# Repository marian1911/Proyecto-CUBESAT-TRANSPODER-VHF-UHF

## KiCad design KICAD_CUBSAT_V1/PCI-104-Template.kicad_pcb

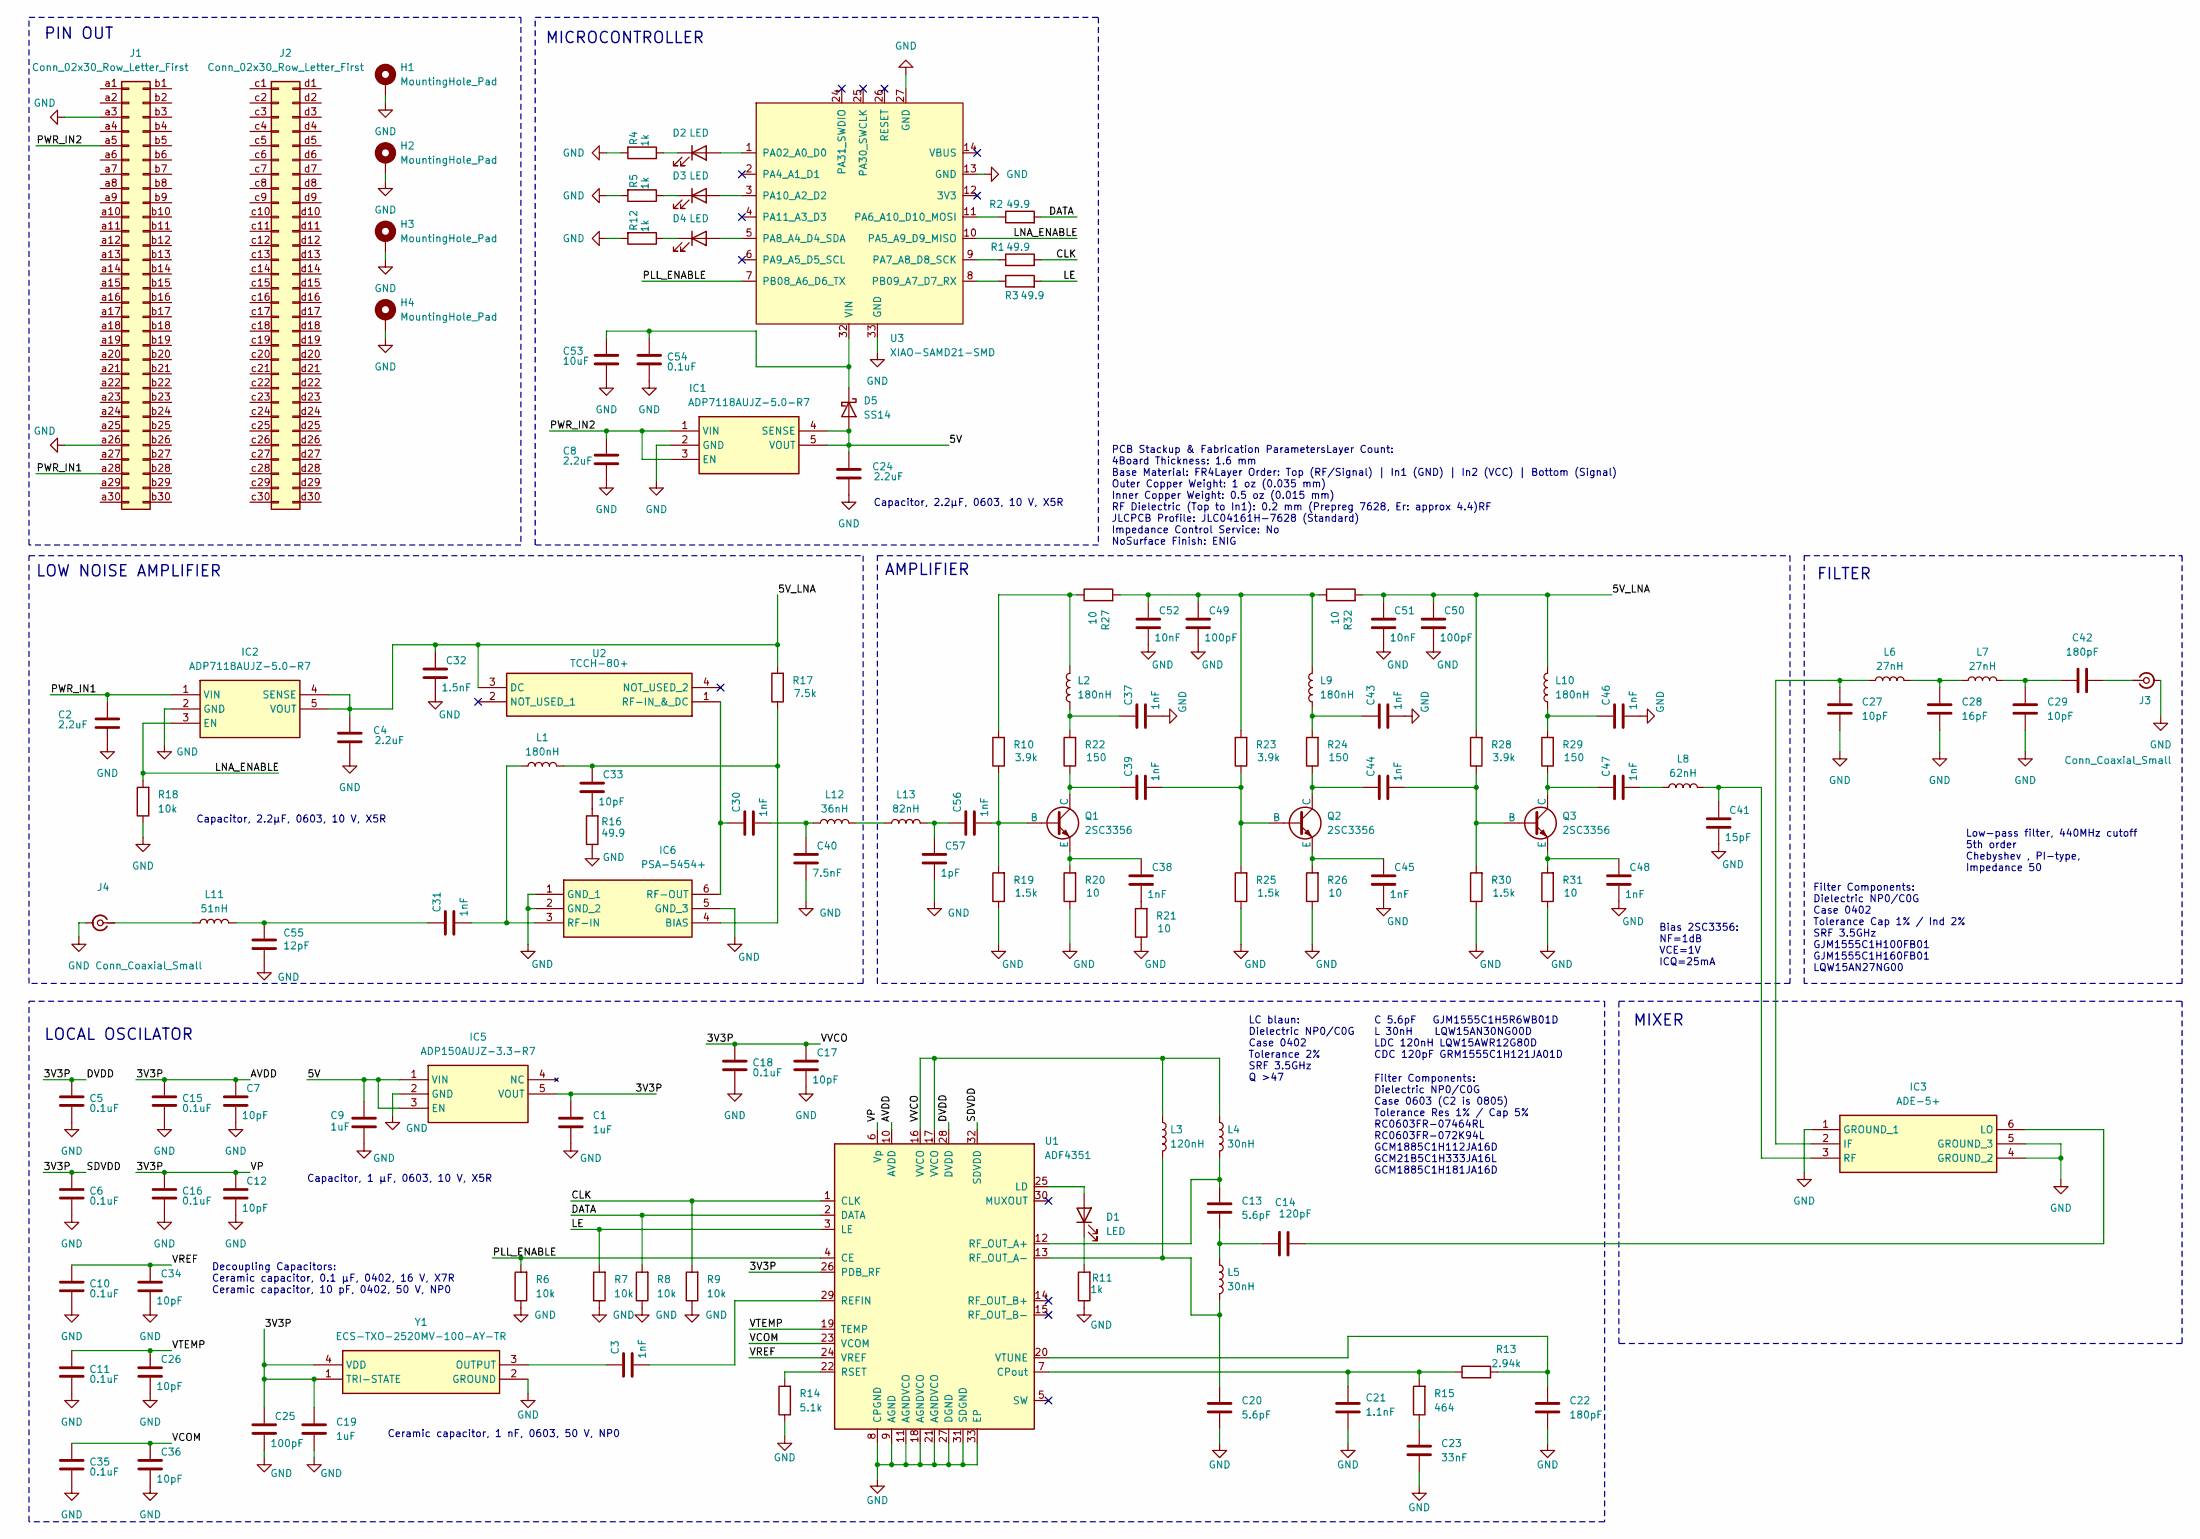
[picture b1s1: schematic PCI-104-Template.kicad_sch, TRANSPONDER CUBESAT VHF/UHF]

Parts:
C1, C9, C19: 1uF; C_0603_1608Metric; Mouser Part Number 81-GRM185R61A105KE26
C2, C4, C8, C24: 2.2uF; C_0603_1608Metric; Mouser Part Number 81-GRM188R61C225KADJ
C3, C30, C31, C37, C38, C39, C43, C44, C45, C46, C47, C48, C56: 1nF; C_0603_1608Metric; Manufacturer_Part_Number GRM1885C1H102JA01D; Mouser Part Number 81-GRM39C102J50
C5, C6, C10, C11, C15, C16, C18, C35, C54: 0.1uF; C_0402_1005Metric; Manufacturer_Part_Number GRM155R71C104KA88D; Mouser Part Number 81-GRM155R71C104KA88
C7, C12, C17, C26, C33, C34, C36: 10pF; C_0402_1005Metric; Manufacturer_Part_Number GRM1555C1H100JA01D; Mouser Part Number 81-GRM1555C1H100JA1D
C13, C20: 5.6pF; C_0402_1005Metric; Manufacturer_Part_Number GJM1555C1H5R6WB01D; Mouser Part Number 81-GJM1555C1H5R6WB1D
C14: 120pF; C_0402_1005Metric; Mouser Part Number 81-GRM1555C1H121JA01
C21: 1.1nF; C_0603_1608Metric; Mouser Part Number 81-GCM1885C1H112JA6D
C22, C42: 180pF; C_0603_1608Metric; Mouser Part Number 81-GCM1885C1H181J16D
C23: 33nF; C_0805_2012Metric; Mouser Part Number 81-GCM21B5C2A333GE2L
C25, C49, C50: 100pF; C_0402_1005Metric; Manufacturer_Part_Number GRM1885C1H101JA01D; Mouser Part Number 81-GRM39C101J50
C27, C29: 10pF; C_0402_1005Metric; Manufacturer_Part_Number GJM1555C1H100FB01D; Mouser Part Number 81-GJM1555C1H100FB01
C28: 16pF; C_0402_1005Metric; Manufacturer_Part_Number GJM1555C1H160FB01J; Mouser Part Number 81-GJM1555C1H160FB1J
C32: 1.5nF; C_0603_1608Metric; Manufacturer_Part_Number GRM1885C1H152JA01J; Mouser Part Number 81-GRM185C1H152JA01J
C40: 7.5nF; C_0603_1608Metric; Manufacturer_Part_Number GRM0225C1E7R5BA03L; Mouser Part Number 81-GRM0225C1E7R5BA3L
C41: 15pF; C_0402_1005Metric; Manufacturer_Part_Number GJM0225C1E150GB01L; Mouser Part Number 81-GJM0225C1E150GB1L
C51, C52: 10nF; C_0402_1005Metric; Manufacturer_Part_Number GRM1885C1H103JA01D; Mouser Part Number 81-GRM1885C1H103JA1D
C53: 10uF; C_0805_2012Metric; Mouser Part Number 81-GRT21BR61E106KE3L
C55: 12pF; C_0402_1005Metric; Manufacturer_Part_Number GJM0225C1C120JB01L; Mouser Part Number 81-GJM0225C1C120JB1L
C57: 1pF; C_0603_1608Metric; Manufacturer_Part_Number GJM0225C1E1R0CB01L; Mouser Part Number 81-GJM0225C1E1R0CB1L
D1, D2, D3, D4: LED; LED_0603_1608Metric; Manufacturer_Part_Number LTST-C190GKT; Mouser Part Number 859-LTST-C190GKT
D5: SS14; D_SMA; Mouser Part Number 512-SS14
H1, H2, H3, H4: MountingHole_Pad; MountingHole_3.2mm_M3_Pad_TopBottom
IC1, IC2: ADP7118AUJZ-5.0-R7; SOT95P280X100-5N; Mouser Part Number 584-ADP7118AUJZ5.0R7
IC3: ADE-5+; ADE5; Mouser Part Number 139-ADE-5
IC5: ADP150AUJZ-3.3-R7; SOT95P280X100-5N; Mouser Part Number 584-ADP150AUJZ3.3R7
IC6: PSA-5454+; SOT65P215X100-6N; Mouser Part Number 139-PSA-5454
J1, J2: Conn_02x30_Row_Letter_First; PinSocket_2x30_P2.00mm_Vertical
J3, J4: Conn_Coaxial_Small; SMA_Samtec_SMA-J-P-H-ST-EM1_EdgeMount; Manufacturer_Part_Number SMA-J-P-H-ST-EM1; Mouser Part Number 200-SMAJPHSTEM1
L1, L2, L9, L10: 180nH; L_0402_1005Metric; Manufacturer_Part_Number LQW15AWR18J80D; Mouser Part Number 81-LQW15AWR18J80D
L3: 120nH; L_0402_1005Metric; Manufacturer_Part_Number LQW15AWR12G80D; Mouser Part Number 81-LQW15AWR12G80D
L4, L5: 30nH; L_0402_1005Metric; Manufacturer_Part_Number LQW15AN30NG00D; Mouser Part Number 81-LQW15AN30NG00D
L6, L7: 27nH; L_0402_1005Metric; Manufacturer_Part_Number LQW15AN27NG00D; Mouser Part Number 81-LQW15AN27NG00D
L8: 62nH; L_0402_1005Metric; Manufacturer_Part_Number LQW15AN62NJ0ZD; Mouser Part Number 81-LQW15AN62NJ0ZD
L11: 51nH; L_0402_1005Metric; Manufacturer_Part_Number LQW15AN51NH0ZD; Mouser Part Number 81-LQW15AN51NH0ZD
L12: 36nH; L_0402_1005Metric; Manufacturer_Part_Number LQW15AN36NG80D; Mouser Part Number 81-LQW15AN36NG80D
L13: 82nH; L_0402_1005Metric; Manufacturer_Part_Number LQW15AW82NG80D; Mouser Part Number 81-LQW15AW82NG80D
Q1, Q2, Q3: 2SC3356; SOT-23
R1, R2, R3, R16: 49.9; R_0603_1608Metric; Manufacturer_Part_Number TNPW060349R9FEEA; Mouser Part Number 71-TNPW060349R9FEEA
R4, R5, R11, R12: 1k; R_0603_1608Metric; Mouser Part Number 71-TNPW06031K00FHEA
R6, R7, R8, R9, R18: 10k; R_0603_1608Metric; Mouser Part Number 71-TNPW060310K0FEEA
R10, R23, R28: 3.9k; R_0603_1608Metric; Manufacturer_Part_Number MCT06030C3901FP500; Mouser Part Number 594-MCT06030C3901FP5
R13: 2.94k; R_0603_1608Metric; Manufacturer_Part_Number RC0603FR-072K94L; Mouser Part Number 603-RC0603FR-072K94L
R14: 5.1k; R_0603_1608Metric; Manufacturer_Part_Number TNPW06035K10FHTA; Mouser Part Number 71-TNPW06035K10FHTA
R15: 464; R_0603_1608Metric; Manufacturer_Part_Number RC0603FR-07464RL; Mouser Part Number 603-RC0603FR-07464RL
R17: 7.5k; R_0603_1608Metric; Manufacturer_Part_Number MCT0603MD7501BP500; Mouser Part Number 594-MCT0603MD7501BP5
R19, R25, R30: 1.5k; R_0603_1608Metric; Manufacturer_Part_Number MCT0603MC1501FP500; Mouser Part Number 594-MCT0603MC1501FP5
R20, R21, R26, R27, R31, R32: 10; R_0603_1608Metric; Manufacturer_Part_Number MCT06030C1009FP500; Mouser Part Number 594-MCT06030C1009FP5
R22, R24, R29: 150; R_0603_1608Metric; Manufacturer_Part_Number MCT06030C1500FP500; Mouser Part Number 594-MCT06030C1500FP5
U1: ADF4351; LFCSP-32-1EP_5x5mm_P0.5mm_EP3.25x3.25mm; Manufacturer_Part_Number ADF4351BCPZ; Mouser Part Number 584-ADF4351BCPZ
U2: TCCH-80+; TCCH80; Mouser Part Number 139-TCCH-80
U3: XIAO-SAMD21-SMD; Manufacturer_Part_Number 102010328; Mouser Part Number 713-102010328
Y1: ECS-TXO-2520MV-100-AY-TR; ECSTXO2520MV120AYTR; Mouser Part Number 520-TXO2520MV100AYTR

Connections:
/3V3P: C1.2, C5.2, C6.2, C7.2, C12.2, C15.2, C16.2, C17.2, C18.2, C19.2, C25.2, IC5.5 (VOUT), L3.1, L4.1, U1.6 (Vp), U1.10 (AVDD), U1.16 (VVCO), U1.17 (VVCO), U1.26 (PDB_RF), U1.28 (DVDD), U1.32 (SDVDD), Y1.1 (TRI-STATE), Y1.4 (VDD)
/5V: C9.2, C24.2, D5.2 (A), IC1.4 (SENSE), IC1.5 (VOUT), IC5.1 (VIN), IC5.3 (EN)
/5V_LNA: C4.2, C32.2, C50.2, C51.2, IC2.4 (SENSE), IC2.5 (VOUT), L10.2, R17.2, R28.2, R32.2, U2.3 (DC)
/CLK: R1.2, R9.2, U1.1 (CLK)
/DATA: R2.2, R8.2, U1.2 (DATA)
/LE: R3.2, R7.2, U1.3 (LE)
/LNA_ENABLE: IC2.3 (EN), R18.2, U3.10 (PA5_A9_D9_MISO)
/PLL_ENABLE: R6.2, U1.4 (CE), U3.7 (PB08_A6_D6_TX)
/PWR_IN1: C2.2, IC2.1 (VIN), J1.a28
/PWR_IN2: C8.2, IC1.1 (VIN), IC1.3 (EN), J1.a5
/VCOM: C35.2, C36.2, U1.23 (VCOM)
/VREF: C10.2, C34.2, U1.24 (VREF)
/VTEMP: C11.2, C26.2, U1.19 (TEMP)
GND: C1.1, C2.1, C4.1, C5.1, C6.1, C7.1, C8.1, C9.1, C10.1, C11.1, C12.1, C15.1, C16.1, C17.1, C18.1, C19.1, C20.1, C21.1, C22.1, C23.1, C24.1, C25.1, C26.1, C27.1, C28.1, C29.1, C32.1, C34.1, C35.1, C36.1, C37.1, C40.1, C41.1, C43.1, C45.1, C46.1, C48.1, C49.1, C50.1, C51.1, C52.1, C53.1, C54.1, C55.1, C57.1, H1.1, H2.1, H3.1, H4.1, IC1.2 (GND), IC2.2 (GND), IC3.1 (GROUND_1), IC3.4 (GROUND_2), IC3.5 (GROUND_3), IC5.2 (GND), IC6.1 (GND_1), IC6.2 (GND_2), IC6.5 (GND_3), J1.a3, J1.a26, J3.2 (Ext), J4.2 (Ext), R4.2, R5.2, R6.1, R7.1, R8.1, R9.1, R11.1, R12.2, R14.1, R16.1, R18.1, R19.1, R20.1, R21.1, R25.1, R26.1, R30.1, R31.1, U1.8 (CPGND), U1.9 (AGND), U1.11 (AGNDVCO), U1.18 (AGNDVCO), U1.21 (AGNDVCO), U1.27 (DGND), U1.31 (SDGND), U1.33 (EP), U3.13 (GND), U3.27 (GND), U3.33 (GND), Y1.2 (GROUND)
unnamed: C13.1, C14.1, L5.1
unnamed: C23.2, R15.1
unnamed: C28.2, L6.2, L7.1
unnamed: C29.2, C42.2, L7.2
unnamed: C30.1, C40.2, L12.1
unnamed: C31.2, C55.2, L11.2
unnamed: C33.1, R16.2
unnamed: C37.2, L2.1, R22.2
unnamed: C38.1, R21.2
unnamed: C43.2, L9.1, R24.2
unnamed: C46.2, L10.1, R29.2
unnamed: C47.1, L8.1
unnamed: C49.2, C52.2, L9.2, R23.2, R27.2, R32.1
unnamed: C56.2, C57.2, L13.2
unnamed: D1.2 (A), U1.25 (LD)
unnamed: D1.1 (K), R11.2
unnamed: D2.2 (A), U3.1 (PA02_A0_D0)
unnamed: D2.1 (K), R4.1
unnamed: D3.2 (A), U3.3 (PA10_A2_D2)
unnamed: D3.1 (K), R5.1
unnamed: D4.2 (A), U3.5 (PA8_A4_D4_SDA)
unnamed: D4.1 (K), R12.1
unnamed: C53.2, C54.2, D5.1 (K), U3.32 (VIN)
unnamed: C27.2, IC3.2 (IF), L6.1
unnamed: C14.2, IC3.6 (LO)
unnamed: C41.2, IC3.3 (RF), L8.2
unnamed: C33.2, IC6.4 (BIAS), L1.2, R17.1
unnamed: C31.1, IC6.3 (RF-IN), L1.1
unnamed: C30.2, IC6.6 (RF-OUT), U2.1 (RF-IN_&_DC)
unnamed: C42.1, J3.1 (In)
unnamed: J4.1 (In), L11.1
unnamed: L2.2, R10.2, R27.1
unnamed: L12.2, L13.1
unnamed: C56.1, Q1.2 (B), R10.1, R19.2
unnamed: C39.2, Q1.1 (C), R22.1
unnamed: C38.2, Q1.3 (E), R20.2
unnamed: C39.1, Q2.2 (B), R23.1, R25.2
unnamed: C44.2, Q2.1 (C), R24.1
unnamed: C45.2, Q2.3 (E), R26.2
unnamed: C44.1, Q3.2 (B), R28.1, R30.2
unnamed: C47.2, Q3.1 (C), R29.1
unnamed: C48.2, Q3.3 (E), R31.2
unnamed: C21.2, R13.1, R15.2, U1.7 (CPout)
unnamed: C3.1, U1.29 (REFIN)
unnamed: C13.2, L4.2, U1.12 (RF_OUT_A+)
unnamed: C20.2, L3.2, L5.2, U1.13 (RF_OUT_A-)
unnamed: R14.2, U1.22 (RSET)
unnamed: C22.2, R13.2, U1.20 (VTUNE)
unnamed: R2.1, U3.11 (PA6_A10_D10_MOSI)
unnamed: R1.1, U3.9 (PA7_A8_D8_SCK)
unnamed: R3.1, U3.8 (PB09_A7_D7_RX)
unnamed: C3.2, Y1.3 (OUTPUT)

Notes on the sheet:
Capacitor, 1 µF, 0603, 10 V, X5R
Ceramic capacitor, 1 nF, 0603, 50 V, NP0
Filter Components: Dielectric NP0/C0G Case 0402 Tolerance Cap 1% / Ind 2% SRF 3.5GHz GJM1555C1H100FB01 GJM1555C1H160FB01 LQW15AN27NG00
MICROCONTROLLER
Decoupling Capacitors: Ceramic capacitor, 0.1 µF, 0402, 16 V, X7R Ceramic capacitor, 10 pF, 0402, 50 V, NP0
AMPLIFIER
C 5.6pF GJM1555C1H5R6WB01D L 30nH LQW15AN30NG00D LDC 120nH LQW15AWR12G80D CDC 120pF GRM1555C1H121JA01D
MIXER
LC blaun: Dielectric NP0/C0G Case 0402 Tolerance 2% SRF 3.5GHz Q >47
Capacitor, 2.2µF, 0603, 10 V, X5R
FILTER
PCB Stackup & Fabrication ParametersLayer Count: 4Board Thickness: 1.6 mm Base Material: FR4Layer Order: Top (RF/Signal) | In1 (GND) | In2 (VCC) | Bottom (Signal) Outer Copper Weight: 1 oz (0.035 mm) Inner Copper Weight: 0.5 oz (0.015 mm) RF Dielectric (Top to In1): 0.2 mm (Prepreg 7628, Er: approx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
Low-pass filter, 440MHz cutoff 5th order Chebyshev , PI-type, Impedance 50
LOW NOISE AMPLIFIER
LOCAL OSCILATOR
Bias 2SC3356: NF=1dB VCE=1V ICQ=25mA
PIN OUT
Filter Components: Dielectric NP0/C0G Case 0603 (C2 is 0805) Tolerance Res 1% / Cap 5% RC0603FR-07464RL RC0603FR-072K94L GCM1885C1H112JA16D GCM21B5C1H333JA16L GCM1885C1H181JA16D

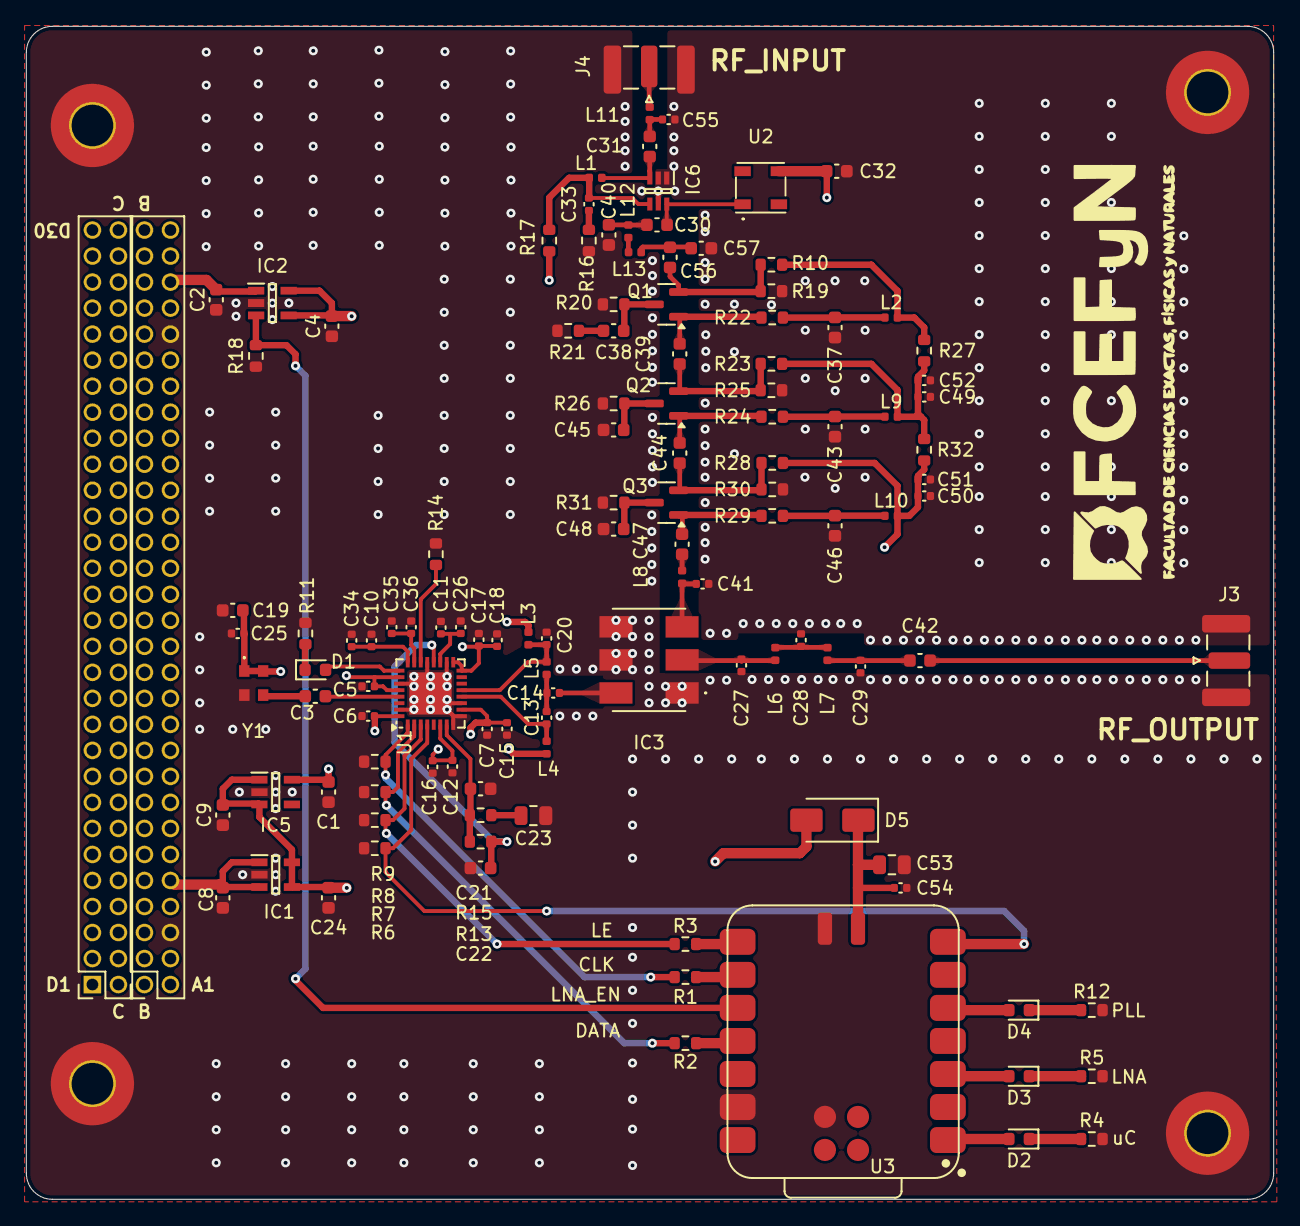
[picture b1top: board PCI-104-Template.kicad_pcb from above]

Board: 4 copper layers, 95.9 x 90.2 mm, 127 parts (0 on the bottom side), 66 nets.

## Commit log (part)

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2026-04-04 calculo de filtro,oscilador,simulaciones
2026-04-04 mejora de filtro
2026-04-05 update BOM
2026-04-08 update part numbers
2026-04-13 update, part number lna y micro
2026-04-15 update simulacion, filtro, microcontrolador, bom final
2026-05-17 mejora lna, 2sc3356
2026-05-20 layout terminado, falta DCR, y aislar micro
2026-06-02 update matching network
2026-06-02 esquema
2026-06-03 update vcc
2026-06-07 match z
